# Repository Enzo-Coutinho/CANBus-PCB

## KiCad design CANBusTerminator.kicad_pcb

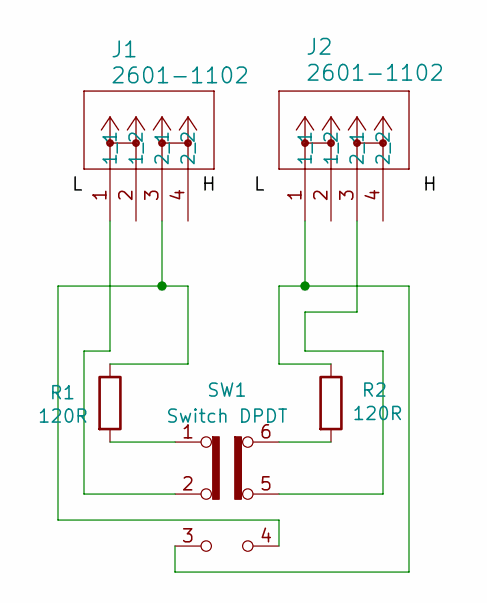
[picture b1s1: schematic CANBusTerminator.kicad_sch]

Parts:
J1, J2: 2601-1102; CONN2_2601-1102_WAG
R1, R2: 120R; R_0805_2012Metric_Pad1.20x1.40mm_HandSolder
SW1: Switch DPDT; SW_CK_JS202011AQN_DPDT_Angled

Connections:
unnamed: J1.1 (1_1), SW1.2 (B)
unnamed: J1.3 (2_1), R1.1, SW1.4 (A)
unnamed: J2.1 (1_1), R2.1, SW1.3 (C)
unnamed: J2.3 (2_1), SW1.5 (B)
unnamed: R1.2, SW1.1 (A)
unnamed: R2.2, SW1.6 (C)

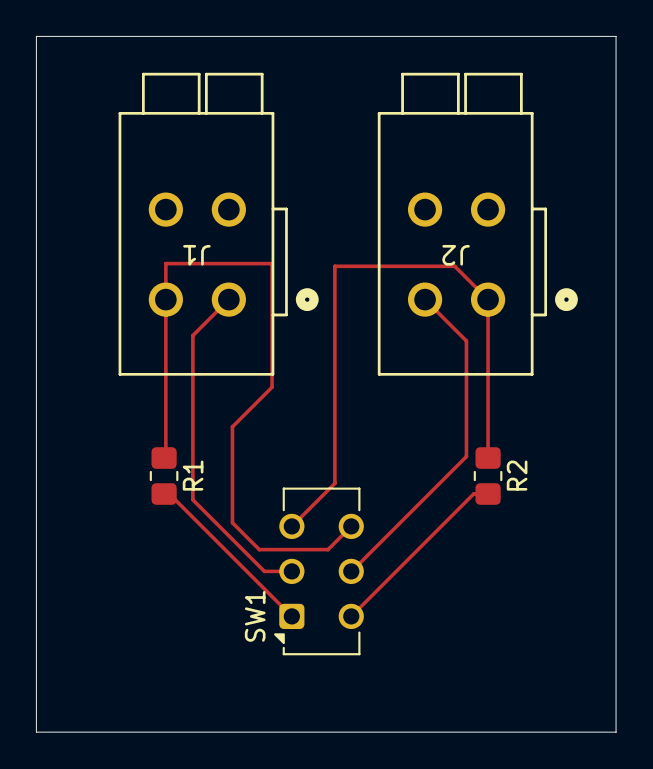
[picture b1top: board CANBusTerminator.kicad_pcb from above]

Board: 2 copper layers, 32.2 x 38.7 mm, 5 parts (0 on the bottom side), 6 nets.

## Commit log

2025-08-16 Add PCB
2025-08-19 feat: add gbr
2025-10-08 feat: put Wago connector .step
2026-05-23 refactor: change to EasyEDA Pro
2026-05-23 update board
2026-05-24 update sch
